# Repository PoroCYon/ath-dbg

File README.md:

# ath-dbg

Adapter and level shifter PCB for debugging the Xtensa CPU in WiFi modules for
the Nintendo DSi.

## Usage

Mount a module on J1. If desired, also use J4 to connect the UART and ERST
signals to the corresponding testpoints on the module. This latter thing will
require some soldering.

Either use the external connectors (J2/J3, J5, J6) or solder a Raspberry Pico
directly to the pin holes present for it.

Some software will still be required to actually do JTAG debugging of the Xtensa
Cpu from a computer. Figuring out how exactly this could be made possible is
the reaosn I built this to begin with.

### Raspberry Pico pinouts

* `GP00`: UART RP to Ath/DWM (R2A)
* `GP01`: UART Ath/DWM to RP (A2R)
* `GP02`: JTAG.ERST (debug CPU reset extension)
* `GP03`: JTAG.TRST
* `GP04`: ~{WIFI_RST}
* `GP05`: SPI.~{WP}
* `GP06`: nSEL_ATH (0=Ath/DWM/TWL, 1=NTR wifi)
* `GP07`: 32 kHz clock to DWM
* `GP08`: SPI.CIPO
* `GP09`: SPI.~{CS}
* `GP10`: SPI.SCK
* `GP11`: SPI.COPI
* `GP12`: JTAG.TDO
* `GP13`: JTAG.TCK
* `GP14`: JTAG.TDI
* `GP15`: JTAG.TMS
* `GP16`: SDIO.CLK
* `GP17`: SDIO.D0
* `GP18`: SDIO.D1
* `GP19`: SDIO.D2
* `GP20`: SDIO.D3
* `GP21`: SDIO.CMD
* `GP22`: ATH_TX_H
* `GP26`: nTWLRST (DSi system reset)
* `GP27`: nDETECT (0=DWM inserted)
* `GP28`: JTAG.CPURST (CPU reset if JTAG.ERST=1 on boot. else ~{WIFI_RST} is the reset)

## Bill of Materials

| Reference | Value  | Footprint           | Notes |
|:--------- |:------ |:------------------- |:----- |
| C1, C3    | 1 uF   | 0603                | 1V8 LDO cap |
| C3-C8     | 100 nF | 0603                | decoupling caps |
| J1        | Molex SlimStack 52991-0508 | | WiFi module connector. must be this exact part number. |
| J2        | 1x9-pin header | 2.54mm pitch | |
| J3        | 10-pin Cortex Debug connector | 1.27mm | dual SMD/THT footprint |
| J4        | 1x6-pin header | 2.54mm pitch | |
| J5        | 1x8-pin header | 2.54mm pitch | |
| J6        | 1x4-pin header | 2.54mm pitch | |
| R1-R6     | 22 Ohm         | 0603         | |
| R7-R17    | 47 kOhm        | 0603         | |
| U1        | Raspberry Pico | Raspberry Pico | |
| U2        | 3.3V-&gt;1.8V LDO | SOT-23-5  | TI TLV70018DDC, Diodes AP7343D-18W5-7 |
| U3-U5     | 3.3V&lt;-&gt;1.8V level shifter | TSSOP-14 | TI TXU0304, Nexperia NXU0304 |

## Dependencies

RP2040 and Raspberry Pico symbols and footprints from [here
](https://github.com/ncarandini/KiCad-RP-Pico).

## License

[CERN-OHL-S v2](./LICENSE)

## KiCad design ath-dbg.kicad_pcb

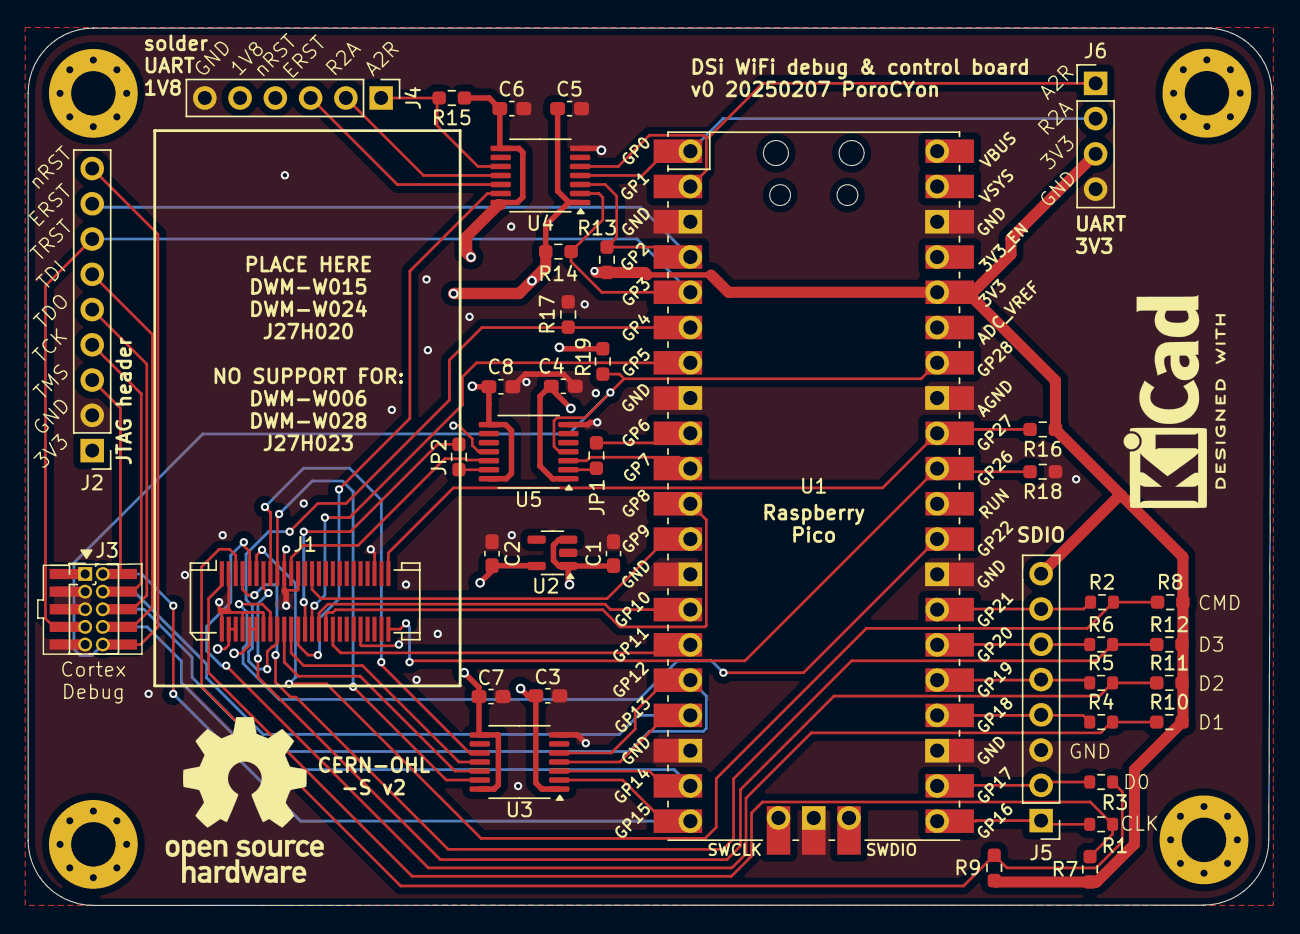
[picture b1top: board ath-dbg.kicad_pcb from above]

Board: 4 copper layers, 89.6 x 63.2 mm, 45 parts (0 on the bottom side), 48 nets.

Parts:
C1, C2: 1u; C_0603_1608Metric_Pad1.08x0.95mm_HandSolder
C3, C4, C5, C6, C7, C8: 100n; C_0603_1608Metric_Pad1.08x0.95mm_HandSolder
H1, H2, H3, H4: MountingHole; MountingHole_3.2mm_M3_Pad_Via
J1: TWL_WifiConn_Rcpt; Molex_SlimStack_52991-0508_2x25_P0.50mm_Vertical
J2: Conn_01x09; PinHeader_1x09_P2.54mm_Vertical
J3: CortexDbgConn; PinHeader_2x05_P1.27mm_Vertical
J4: Conn_01x05; PinHeader_1x06_P2.54mm_Vertical
J5: Conn_01x08; PinHeader_1x08_P2.54mm_Vertical
J6: Conn_01x04; PinHeader_1x04_P2.54mm_Vertical
J10: CortexDbgConn SMD; PinHeader_2x05_P1.27mm_Vertical_SMD
JP1, JP2: SolderJumper_2_Open; R_0603_1608Metric_Pad0.98x0.95mm_HandSolder
R1, R2, R3, R4, R5, R6: 22; R_0603_1608Metric
R7, R8, R9, R10, R11, R12, R13, R14, R15, R16, R17, R18, R19: 47k; R_0603_1608Metric_Pad0.98x0.95mm_HandSolder
U1: Pico; RPi_Pico_SMD_TH
U2: TLV70018DDC; SOT-23-5
U3, U4, U5: TXU0304; TSSOP-14_4.4x5mm_P0.65mm

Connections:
+1V8: C2.1, C6.1, C7.1, C8.1, J1.4 (VDD18), J1.6 (VDD18), J4.5, R15.1, U2.5 (OUT), U3.8 (OE), U3.14 (V_{CCB}), U4.8 (OE), U4.14 (V_{CCB}), U5.8 (OE), U5.14 (V_{CCB})
+3V3: C1.1, C3.1, C4.1, C5.1, J1.10 (VDD33), J1.12 (VDD33), J2.1, J3.1, J5.8, J6.3, J10.1, R7.2, R8.2, R9.2, R10.2, R11.2, R12.2, R13.1, R14.1, R16.1, R19.1, U1.36 (3V3), U2.1 (IN), U2.3 (EN), U3.1 (V_{CCA}), U4.1 (V_{CCA}), U5.1 (V_{CCA})
/CLK': J5.1, R1.1, U1.21 (GPIO16)
/CMD': J5.7, R2.1, U1.27 (GPIO21)
/D0': J5.2, R3.1, U1.22 (GPIO17)
/D1': J5.4, R4.1, U1.24 (GPIO18)
/D2': J5.5, R5.1, U1.25 (GPIO19)
/D3': J5.6, R6.1, U1.26 (GPIO20)
ATH_TX_H: J1.16 (ATH_TX_H), U1.29 (GPIO22)
CIPO: J1.32 (SPI_CIPO), U1.11 (GPIO8)
CLK: J1.1 (SDIO_CLK), R1.2, R7.1
CLK32K_18: J1.21 (RTC_FOUT), U5.12 (B2Y)
CLK32K_33: U1.10 (GPIO7), U5.3 (A2)
CMD: J1.11 (SDIO_CMD), R2.2, R8.1
COPI: J1.34 (SPI_COPI), U1.15 (GPIO11)
D0: J1.5 (SDIO_DAT0), R3.2, R9.1
D1: J1.9 (SDIO_DAT1), R4.2, R10.1
D2: J1.13 (SDIO_DAT2), R5.2, R11.1
D3: J1.7 (SDIO_DAT3), R6.2, R12.1
DET_TWL: J1.49, R16.2, U1.32 (GPIO27_ADC1)
GND: C1.2, C2.2, C3.2, C4.2, C5.2, C6.2, C7.2, C8.2, J1.2 (GND), J1.3 (GND), J1.8 (GND), J1.14 (GND), J1.19 (GND), J1.23 (GND), J1.42 (GND), J1.45 (GND), J2.2, J3.3, J3.5, J3.9, J4.6, J5.3, J6.4, J10.3, J10.5, J10.9, R17.1, R18.1, U1.3 (GND), U1.8 (GND), U1.13 (GND), U1.18 (GND), U1.23 (GND), U1.28 (GND), U1.33 (AGND), U1.38 (GND), U1.42 (GND), U2.2 (GND), U3.7 (GND), U4.7 (GND), U5.7 (GND)
JTAG18.CPURST: J4.4, U5.11 (B3Y)
JTAG18.ERST: J4.3, U4.12 (B2Y)
JTAG18.TCK: J1.22 (JTAG_TCK), U3.11 (B3Y)
JTAG18.TDI: J1.20 (JTAG_TDI), U3.12 (B2Y)
JTAG18.TDO: J1.15 (JTAG_TDO), U3.10 (B4)
JTAG18.TMS: J1.17 (JTAG_TMS), U3.13 (B1Y)
JTAG18.~TRST: J1.24 (JTAG_~TRST), U4.13 (B1Y)
JTAG33.CPURST: J2.9, J3.10, J10.10, R19.2, U1.34 (GPIO28_ADC2), U5.4 (A3)
JTAG33.ERST: J2.8, R13.2, U1.4 (GPIO2), U4.3 (A2)
JTAG33.TCK: J2.4, J3.4, J10.4, U1.17 (GPIO13), U3.4 (A3)
JTAG33.TDI: J2.6, J3.8, J10.8, U1.19 (GPIO14), U3.3 (A2)
JTAG33.TDO: J2.5, J3.6, J10.6, U1.16 (GPIO12), U3.5 (A4Y)
JTAG33.TMS: J2.3, J3.2, J10.2, U1.20 (GPIO15), U3.2 (A1)
JTAG33.~TRST: J2.7, J3.7, J10.7, R14.2, U1.5 (GPIO3), U4.2 (A1)
unnamed: JP1.2 (B), U5.2 (A1)
unnamed: JP2.1 (A), U5.13 (B1Y)
SCK: J1.30 (SPI_SCK), U1.14 (GPIO10)
UART18.ATH2RP: J4.1, R15.2, U4.10 (B4)
UART18.RP2ATH: J4.2, U4.11 (B3Y)
UART33.ATH2RP: J6.1, U1.2 (GPIO1), U4.5 (A4Y)
UART33.RP2ATH: J6.2, U1.1 (GPIO0), U4.4 (A3)
~CS: J1.27 (SPI_~CS2), U1.12 (GPIO9)
~SEL_ATH_18: J1.26 (~SEL_ATH), JP2.2 (B)
~SEL_ATH_33: JP1.1 (A), U1.9 (GPIO6)
~TWLRST: J1.50 (RESET), R18.2, U1.31 (GPIO26_ADC0)
~WIFI_RST: J1.18 (~WIFI_RST), R17.2, U1.6 (GPIO4)
~WP: J1.28 (FLASH_~WP), U1.7 (GPIO5)

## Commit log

2025-02-07 stuff
2025-02-07 reset stuff
2025-02-20 fix typo in readme

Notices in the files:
ath-dbg.kicad_pcb:
CERN OHL v2 strongly reciprocal
